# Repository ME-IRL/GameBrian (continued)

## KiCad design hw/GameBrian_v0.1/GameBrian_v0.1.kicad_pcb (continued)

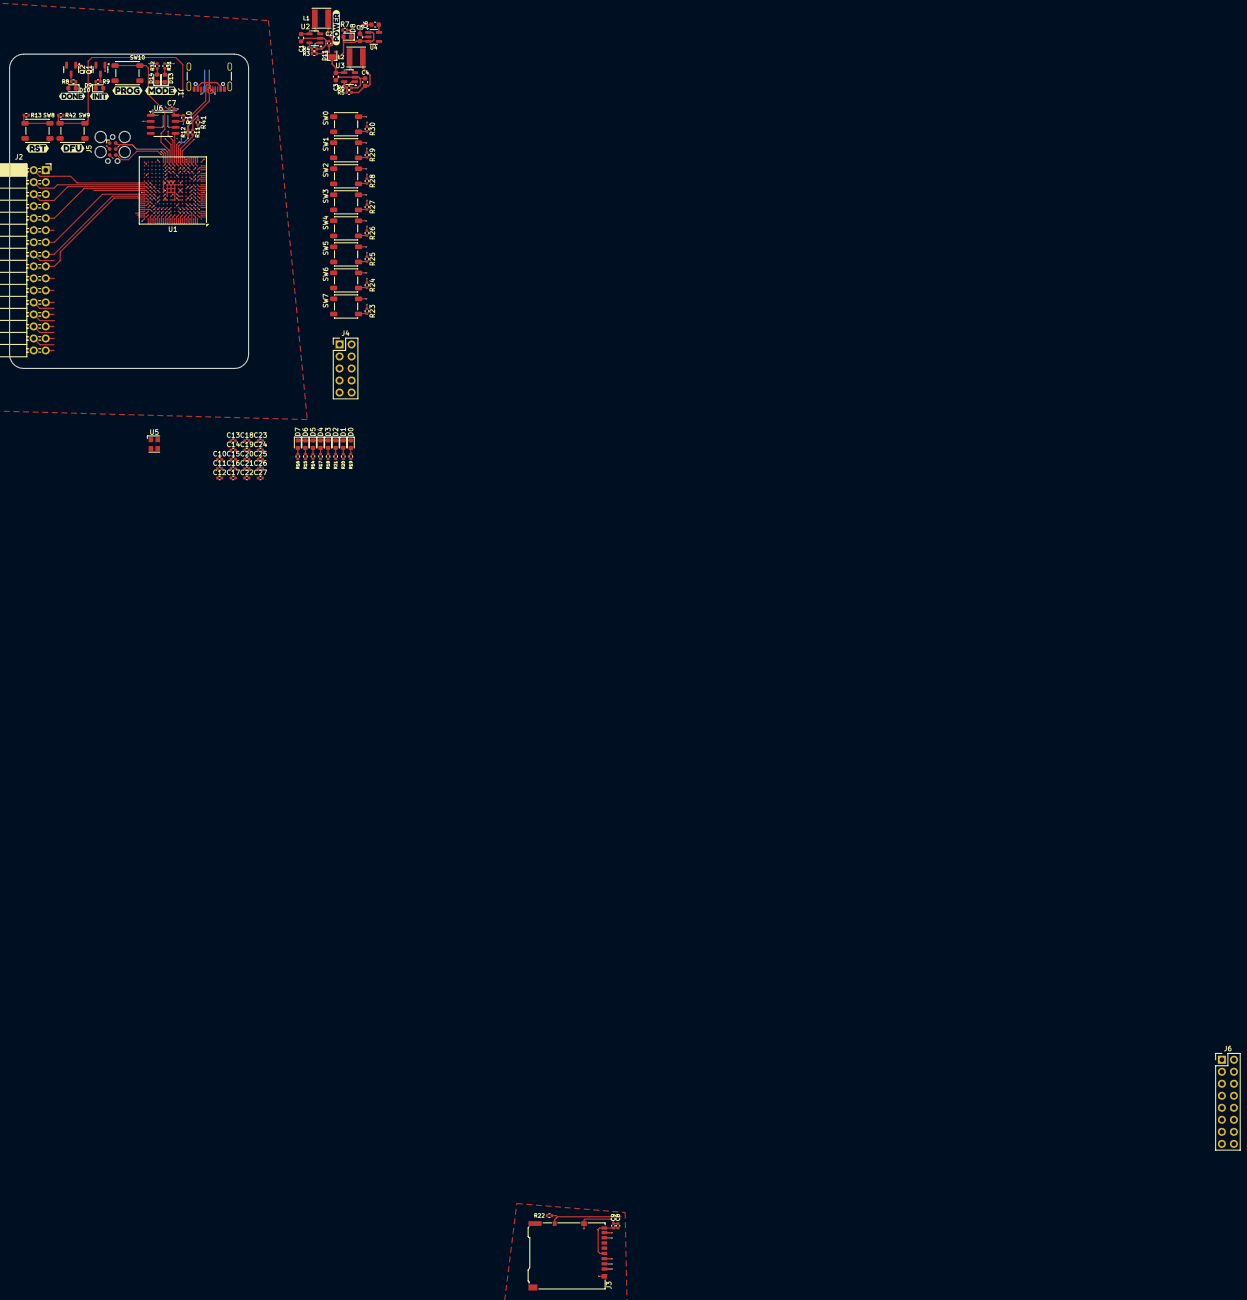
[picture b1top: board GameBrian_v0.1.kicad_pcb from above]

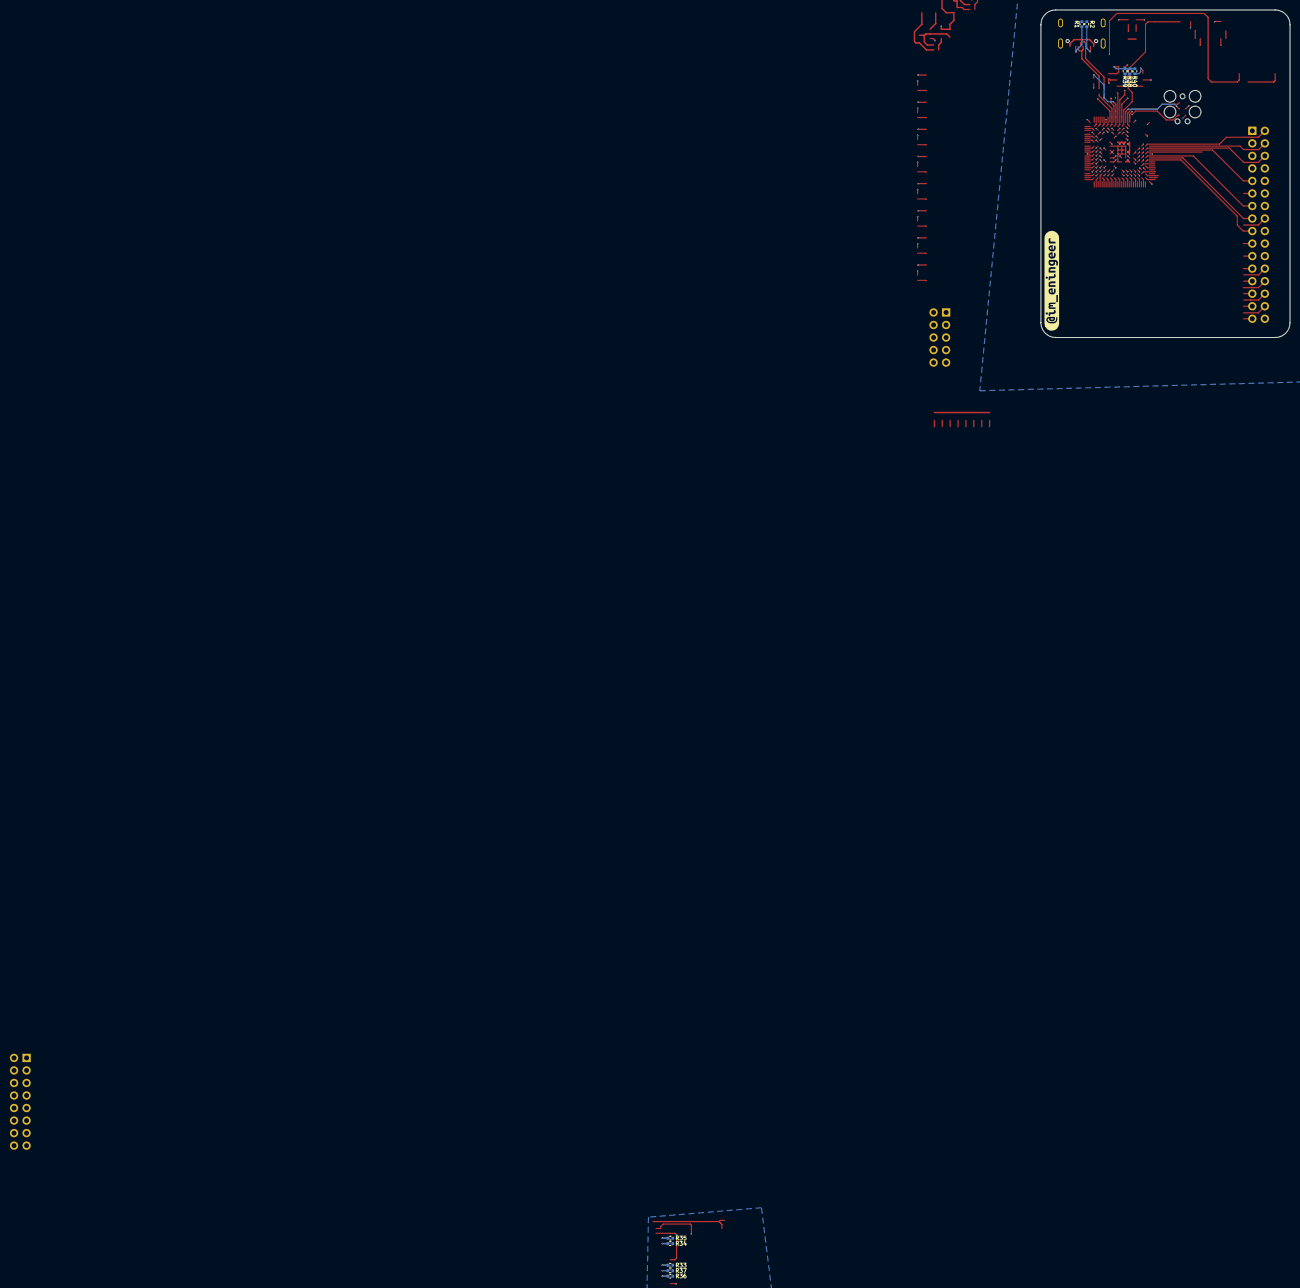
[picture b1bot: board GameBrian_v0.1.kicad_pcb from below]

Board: 6 copper layers, 50.5 x 66.4 mm, 120 parts (11 on the bottom side), 94 nets.

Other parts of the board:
kibuzzard-66DED2DA: G***; kibuzzard-66DED2DA
kibuzzard-66DED4B2: G***; kibuzzard-66DED4B2
kibuzzard-66DED6B8: G***; kibuzzard-66DED6B8
kibuzzard-66DED23A: G***; kibuzzard-66DED23A
kibuzzard-66DED159: G***; kibuzzard-66DED159
kibuzzard-66DED542: G***; kibuzzard-66DED542
kibuzzard-66DED556: G***; kibuzzard-66DED556
kibuzzard-66DEDB5F: G***; kibuzzard-66DEDB5F
kibuzzard-66DEDB75: G***; kibuzzard-66DEDB75
kibuzzard-66DEDB97: G***; kibuzzard-66DEDB97

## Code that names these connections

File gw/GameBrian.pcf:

# Pinout for the iCE40-HX8K Breakout Board

set_io board_clk J3
set_io board_rst B11

#set_io flash_csb R12
#set_io flash_clk R11
#set_io flash_io0 P12
#set_io flash_io1 P11

# for QSPI mode the flash chip on the iCE40-HX8K Breakout Board
# must be replaced with one that supports QSPI and the IO2 and IO3
# pins must be soldered to T9 and P8 (center on J3)
#set_io flash_io2 T9
#set_io flash_io3 P8

set_io ser_tx B12
set_io ser_rx B10

set_io leds[7] B5  # D9
set_io leds[6] B4  # D8
set_io leds[5] A2  # D7
set_io leds[4] A1  # D6
set_io leds[3] C5  # D5
set_io leds[2] C4  # D4
set_io leds[1] B3  # D3
set_io leds[0] C3  # D2

set_io GBA_VDD    P2
set_io GBA_CLK    P1
set_io GBA_nWR    N2
set_io GBA_nRD    N3
set_io GBA_nCS    M1
set_io GBA_AD[0]  M2
set_io GBA_AD[1]  L1
set_io GBA_AD[2]  L3
set_io GBA_AD[3]  K1
set_io GBA_AD[4]  K3
set_io GBA_AD[5]  J1
set_io GBA_AD[6]  J2
set_io GBA_AD[7]  R5 # J3 taken by clk
set_io GBA_AD[8]  H2
set_io GBA_AD[9]  H1
set_io GBA_AD[10] G2
set_io GBA_AD[11] G1
set_io GBA_AD[12] F2
set_io GBA_AD[13] F1
set_io GBA_AD[14] E2
set_io GBA_AD[15] D2
set_io GBA_A[0]   D1
set_io GBA_A[1]   C2
set_io GBA_A[2]   C1
set_io GBA_A[3]   B2
set_io GBA_A[4]   B1
set_io GBA_A[5]   R4
set_io GBA_A[6]   R3
set_io GBA_A[7]   T3
set_io GBA_nCS2   R2
set_io GBA_nREQ   T2

set_io sd_cs   R9
set_io sd_sck  P8
set_io sd_mosi P9
set_io sd_miso T9
set_io sd_det  T8

set_io debug[0] E14
set_io debug[1] D15
set_io debug[2] D14
set_io debug[3] B16
set_io debug[4] F16
set_io debug[5] E16
set_io debug[6] D16
set_io debug[7] C16

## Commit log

2024-09-09 Initial
2024-09-10 Checkpoint (pre-final route)
2024-09-10 Checkpoint (DDR RAM?)
2024-09-27 Wishbone
2024-09-30 SPI (need debug)
2024-09-30 SPI Fixed
2024-09-30 Cleanup makefile + usercode (git hash)
2024-10-01 Verilator lint (SPI)
2024-10-05 UART WIP
